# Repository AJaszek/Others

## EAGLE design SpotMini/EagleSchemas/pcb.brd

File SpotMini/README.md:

Projecting and creating own version of Boston Dynamics Spot

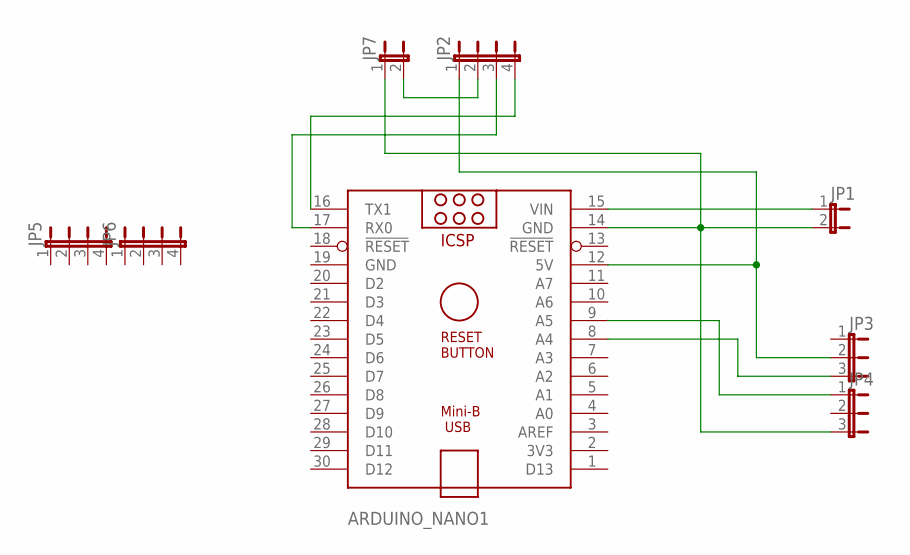
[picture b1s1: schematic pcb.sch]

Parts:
ARDUINO_NANO1: ARDUINO_NANO
JP1, JP7: JP1E; JP1
JP2, JP5, JP6: JP4E; JP4
JP3, JP4: JP2E; JP2

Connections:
GND: ARDUINO_NANO1.19 (GND)
unnamed: ARDUINO_NANO1.15 (VIN), JP1.1
unnamed: ARDUINO_NANO1.14 (GND), JP1.2, JP4.3, JP7.1
unnamed: ARDUINO_NANO1.12 (5V), JP2.1, JP3.2
unnamed: ARDUINO_NANO1.8 (A4), JP3.3
unnamed: ARDUINO_NANO1.9 (A5), JP4.1
unnamed: JP2.2, JP7.2
unnamed: ARDUINO_NANO1.17 (RX0), JP2.3
unnamed: ARDUINO_NANO1.16 (TX1), JP2.4

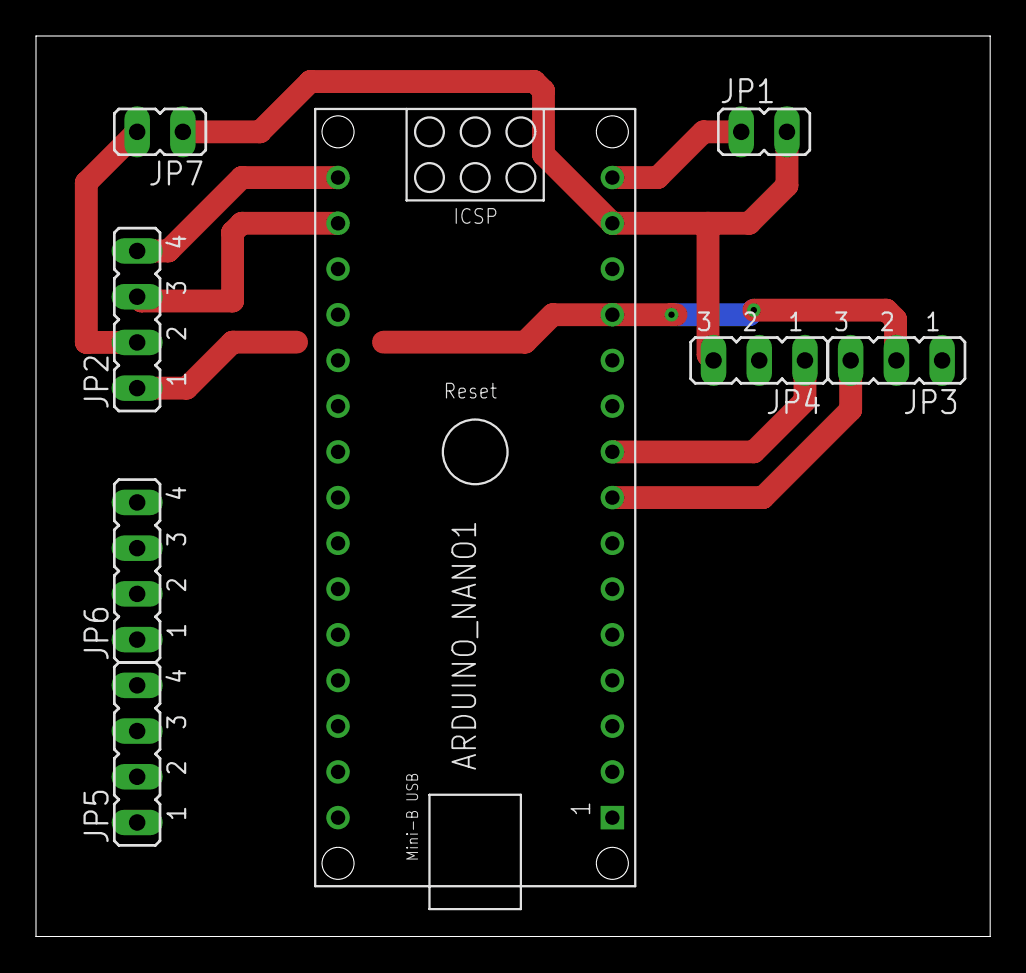
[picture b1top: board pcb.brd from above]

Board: 2 copper layers, 53.0 x 50.0 mm, 8 parts (0 on the bottom side), 8 nets.

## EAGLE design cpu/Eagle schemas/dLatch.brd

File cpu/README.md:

Projecting and creating my own 8-bit cpu

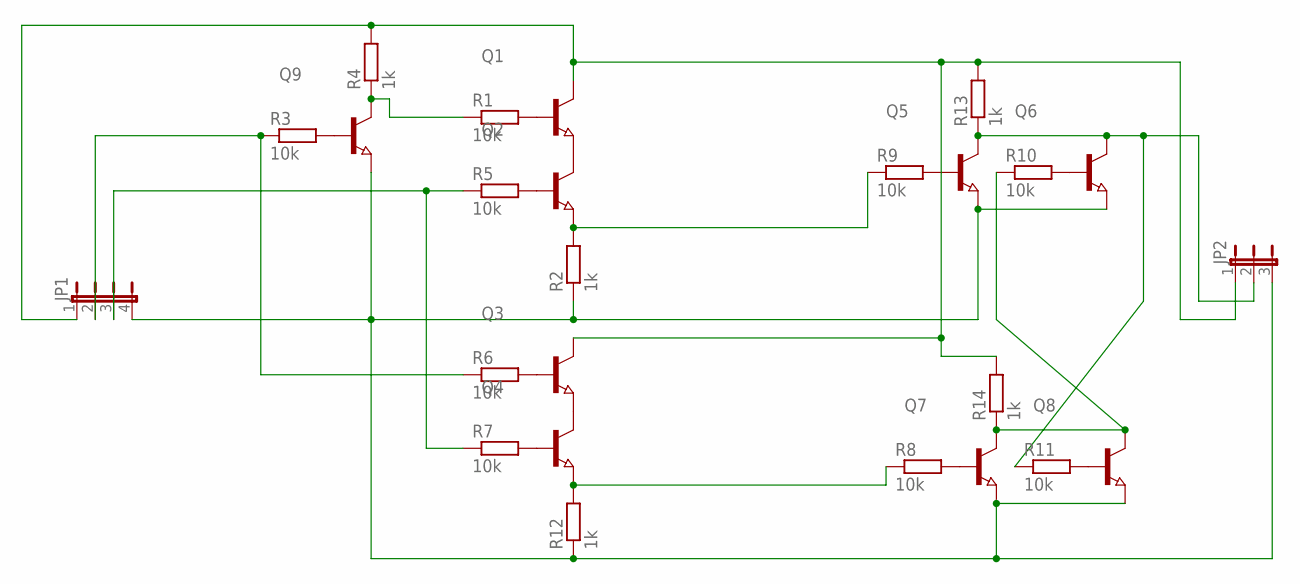
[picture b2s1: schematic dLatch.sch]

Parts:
JP1: JP4E; JP4
JP2: JP2W
Q1, Q2, Q3, Q4, Q5, Q6, Q7, Q8, Q9: NPN-TRANSISTOR_SOT23; SOT23
R1, R3, R5, R6, R7, R8, R9, R10, R11: 10k; R1206
R2, R4, R12, R13, R14: 1k; R1206

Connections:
unnamed: Q1.2 (E), Q2.3 (C)
unnamed: Q3.2 (E), Q4.3 (C)
unnamed: Q2.2 (E), R2.2, R9.1
unnamed: Q1.1 (B), R1.2
unnamed: Q9.1 (B), R3.2
unnamed: Q9.3 (C), R1.1, R4.1
unnamed: Q2.1 (B), R5.2
unnamed: Q3.1 (B), R6.2
unnamed: Q4.1 (B), R7.2
unnamed: Q7.1 (B), R8.2
unnamed: Q5.1 (B), R9.2
unnamed: Q6.1 (B), R10.2
unnamed: Q8.1 (B), R11.2
unnamed: Q4.2 (E), R8.1, R12.2
unnamed: JP2.2, Q5.3 (C), Q6.3 (C), R11.1, R13.1
unnamed: JP1.4, JP2.3, Q5.2 (E), Q6.2 (E), Q7.2 (E), Q8.2 (E), Q9.2 (E), R2.1, R12.1
unnamed: JP1.1, JP2.1, Q1.3 (C), Q3.3 (C), R4.2, R13.2, R14.2
unnamed: Q7.3 (C), Q8.3 (C), R10.1, R14.1
unnamed: JP1.2, R3.1, R6.1
unnamed: JP1.3, R5.1, R7.1

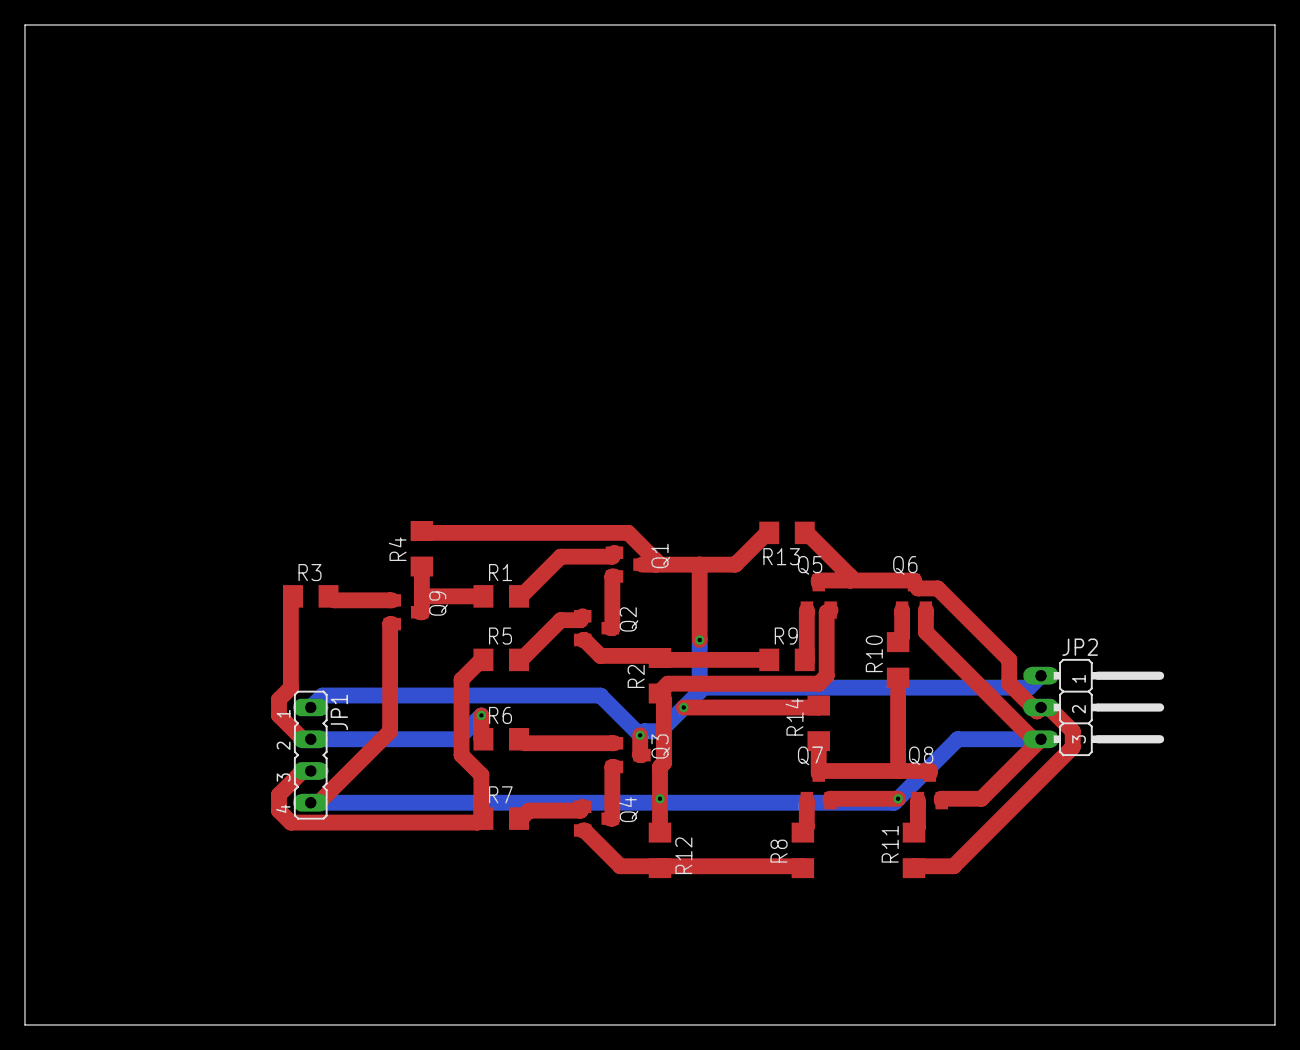
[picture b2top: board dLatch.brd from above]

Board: 2 copper layers, 100.0 x 80.0 mm, 25 parts (0 on the bottom side), 20 nets.

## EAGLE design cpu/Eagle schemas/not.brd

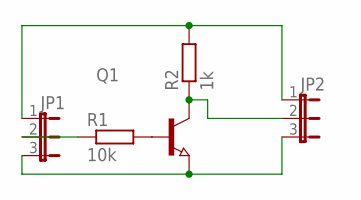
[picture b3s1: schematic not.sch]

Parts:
JP1, JP2: JP2W
Q1: NPN-TRANSISTOR_SOT23; SOT23
R1: 10k; R1206
R2: 1k; R1206

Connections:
unnamed: JP2.2, Q1.3 (C), R2.1
unnamed: Q1.1 (B), R1.2
unnamed: JP1.2, R1.1
unnamed: JP1.3, JP2.3, Q1.2 (E)
unnamed: JP1.1, JP2.1, R2.2

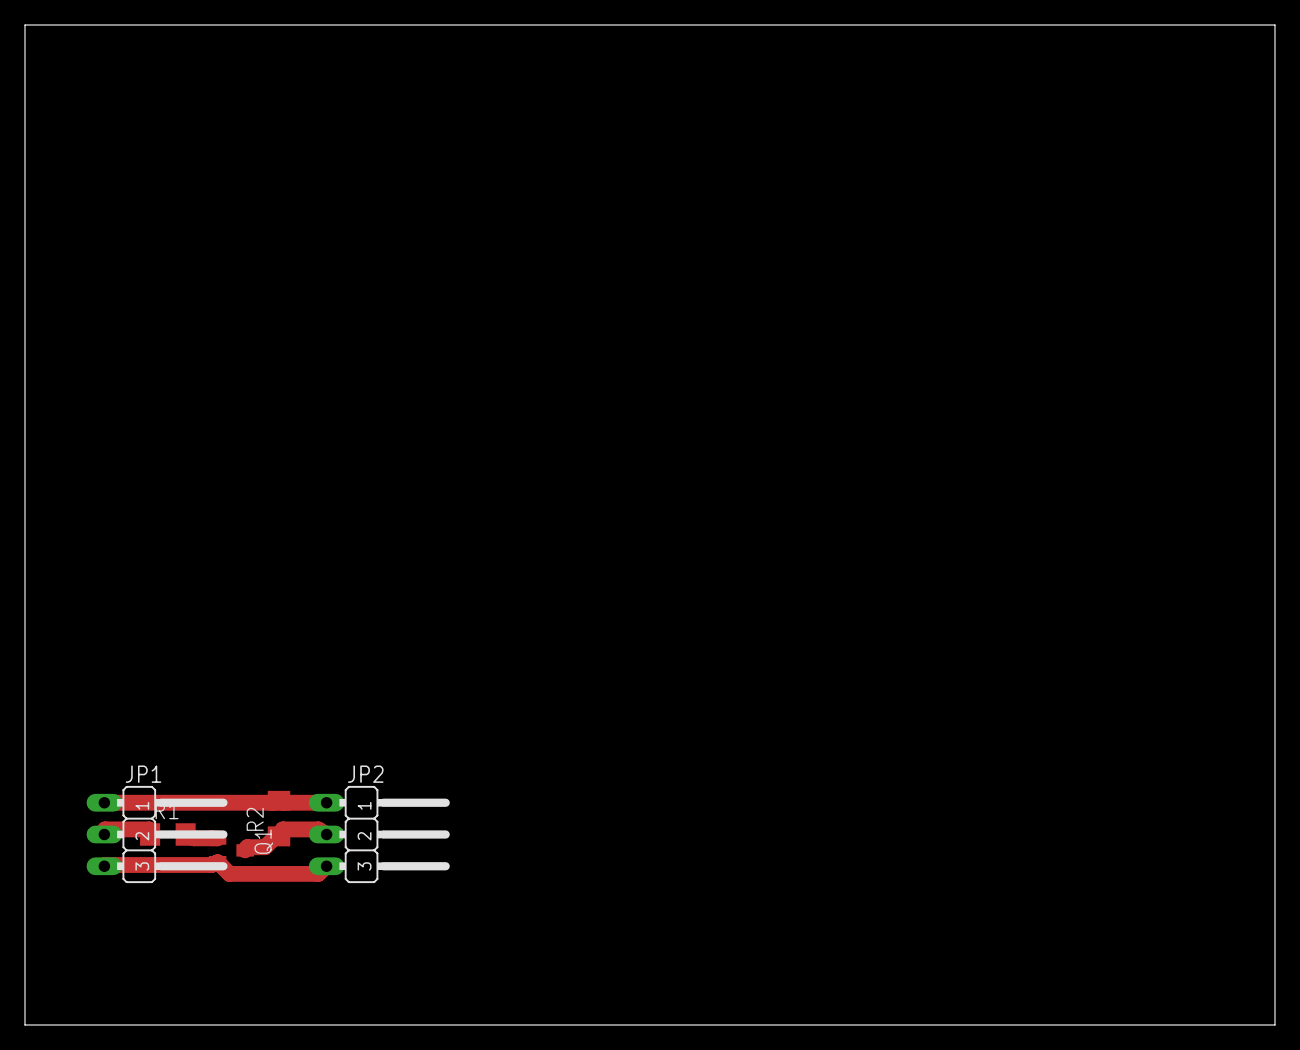
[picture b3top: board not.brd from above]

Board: 2 copper layers, 100.0 x 80.0 mm, 5 parts (0 on the bottom side), 5 nets.

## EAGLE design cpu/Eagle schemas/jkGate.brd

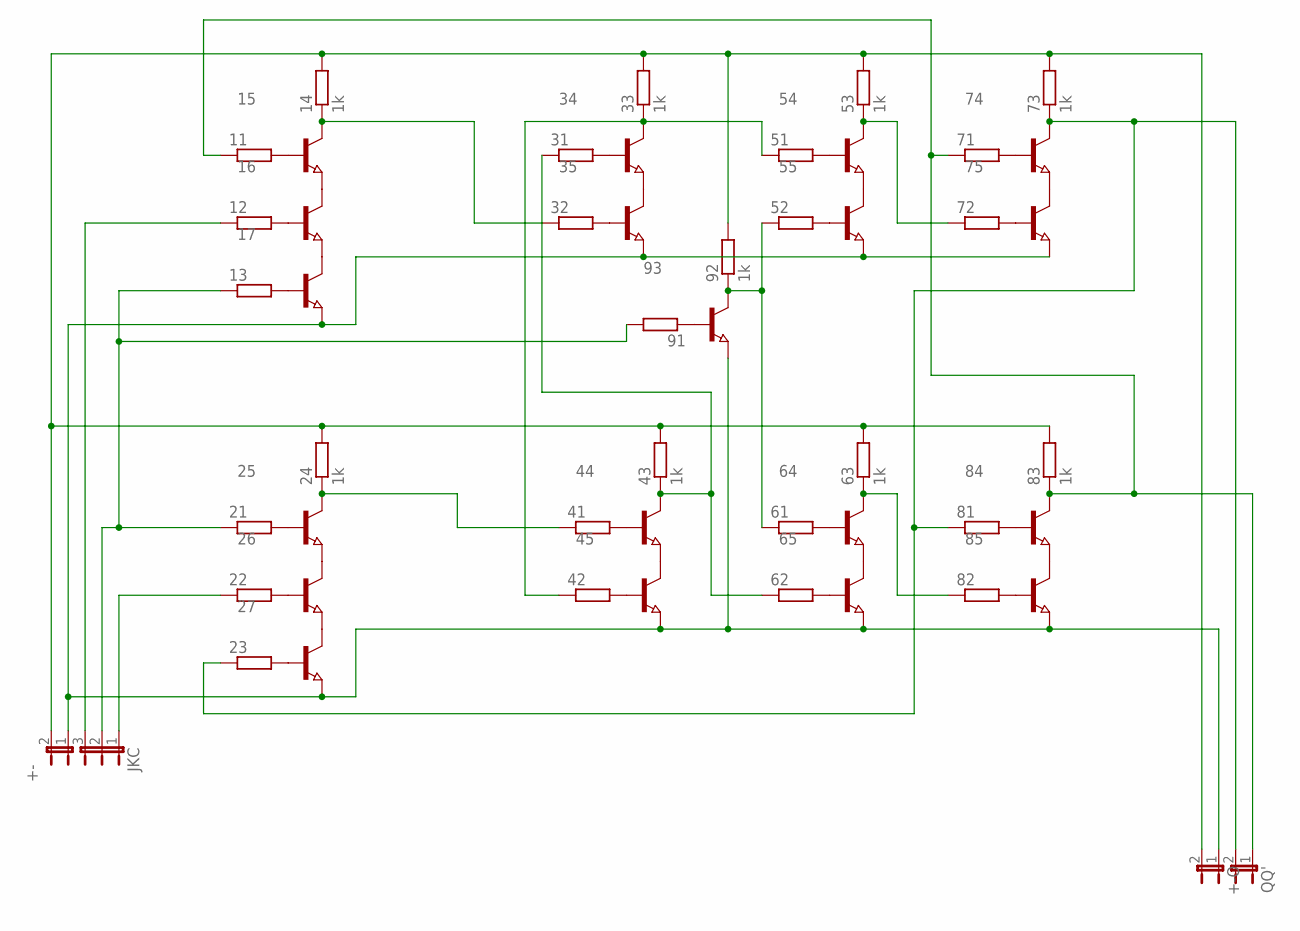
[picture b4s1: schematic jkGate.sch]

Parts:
11, 12, 13, 21, 22, 23, 31, 32, 41, 42, 51, 52, 61, 62, 71, 72, 81, 82, 91: R-EU_R1206; R1206
14, 24, 33, 43, 53, 63, 73, 83, 92: 1k; R1206
15, 16, 17, 25, 26, 27, 34, 35, 44, 45, 54, 55, 64, 65, 74, 75, 84, 85, 93: NPN-TRANSISTOR_SOT23; SOT23
+-: JP1E; JP1
+-O: JP1E; JP1
JKC: JP2E; JP2
QQ': JP1E; JP1

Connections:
5V: 14.2, 24.2, 33.2, 43.2, 53.2, 63.2, 73.2, 83.2, 92.2, +-.2, +-O.2
C: 13.1, 21.1, 91.2, JKC.2
GND: 17.2 (E), 27.2 (E), 35.2 (E), 45.2 (E), 55.2 (E), 65.2 (E), 75.2 (E), 85.2 (E), 93.2 (E), +-.1, +-O.1
J: 12.1, JKC.3
K: 22.1, JKC.1
unnamed: 15.2 (E), 16.3 (C)
unnamed: 16.2 (E), 17.3 (C)
unnamed: 25.2 (E), 26.3 (C)
unnamed: 26.2 (E), 27.3 (C)
unnamed: 34.2 (E), 35.3 (C)
unnamed: 44.2 (E), 45.3 (C)
unnamed: 54.2 (E), 55.3 (C)
unnamed: 64.2 (E), 65.3 (C)
unnamed: 74.2 (E), 75.3 (C)
unnamed: 84.2 (E), 85.3 (C)
unnamed: 21.2, 25.1 (B)
unnamed: 22.2, 26.1 (B)
unnamed: 23.2, 27.1 (B)
unnamed: 11.2, 15.1 (B)
unnamed: 12.2, 16.1 (B)
unnamed: 13.2, 17.1 (B)
unnamed: 31.2, 34.1 (B)
unnamed: 32.2, 35.1 (B)
unnamed: 51.2, 54.1 (B)
unnamed: 52.2, 55.1 (B)
unnamed: 71.2, 74.1 (B)
unnamed: 72.2, 75.1 (B)
unnamed: 81.2, 84.1 (B)
unnamed: 82.2, 85.1 (B)
unnamed: 61.2, 64.1 (B)
unnamed: 62.2, 65.1 (B)
unnamed: 41.2, 44.1 (B)
unnamed: 42.2, 45.1 (B)
unnamed: 24.1, 25.3 (C), 41.1
unnamed: 31.1, 43.1, 44.3 (C), 62.1
unnamed: 63.1, 64.3 (C), 82.1
unnamed: 11.1, 71.1, 83.1, 84.3 (C), QQ'.1
unnamed: 14.1, 15.3 (C), 32.1
unnamed: 33.1, 34.3 (C), 42.1, 51.1
unnamed: 53.1, 54.3 (C), 72.1
unnamed: 23.1, 73.1, 74.3 (C), 81.1, QQ'.2
unnamed: 52.1, 61.1, 92.1, 93.3 (C)
unnamed: 91.1, 93.1 (B)

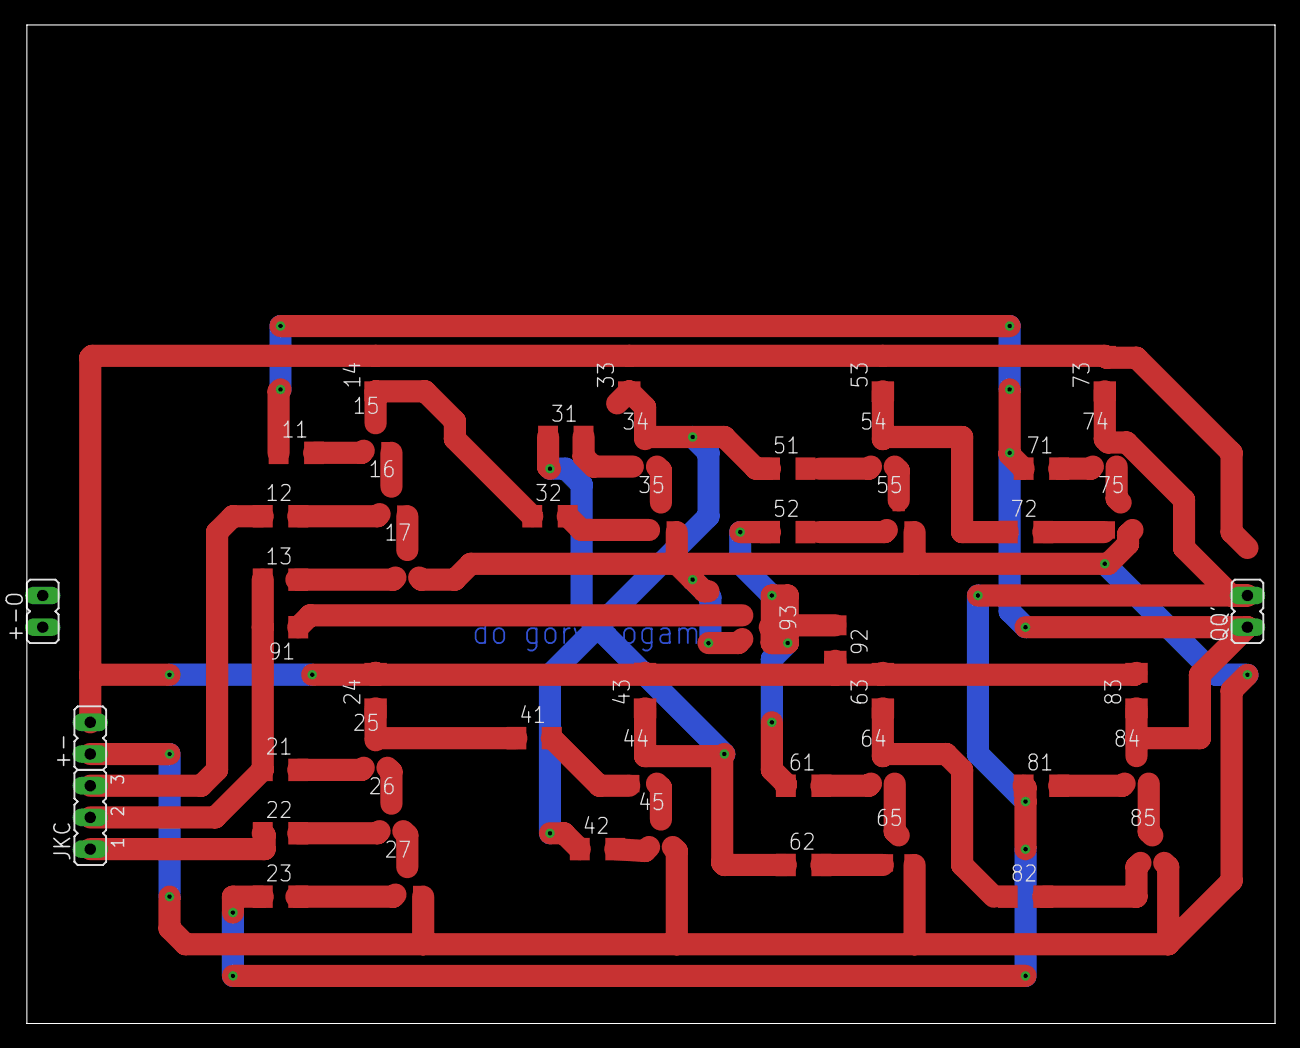
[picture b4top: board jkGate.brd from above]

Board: 2 copper layers, 100.0 x 80.0 mm, 51 parts (0 on the bottom side), 43 nets.

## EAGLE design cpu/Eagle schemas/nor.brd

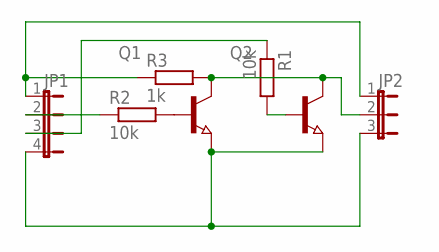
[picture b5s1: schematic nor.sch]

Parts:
JP1: JP4E; JP4
JP2: JP2W
Q1, Q2: NPN-TRANSISTOR_SOT23; SOT23
R1, R2: 10k; R1206
R3: 1k; R1206

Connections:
unnamed: Q2.1 (B), R1.2
unnamed: Q1.1 (B), R2.2
unnamed: JP1.4, JP2.3, Q1.2 (E), Q2.2 (E)
unnamed: JP2.2, Q1.3 (C), Q2.3 (C), R3.2
unnamed: JP1.2, R2.1
unnamed: JP1.3, R1.1
unnamed: JP1.1, JP2.1, R3.1

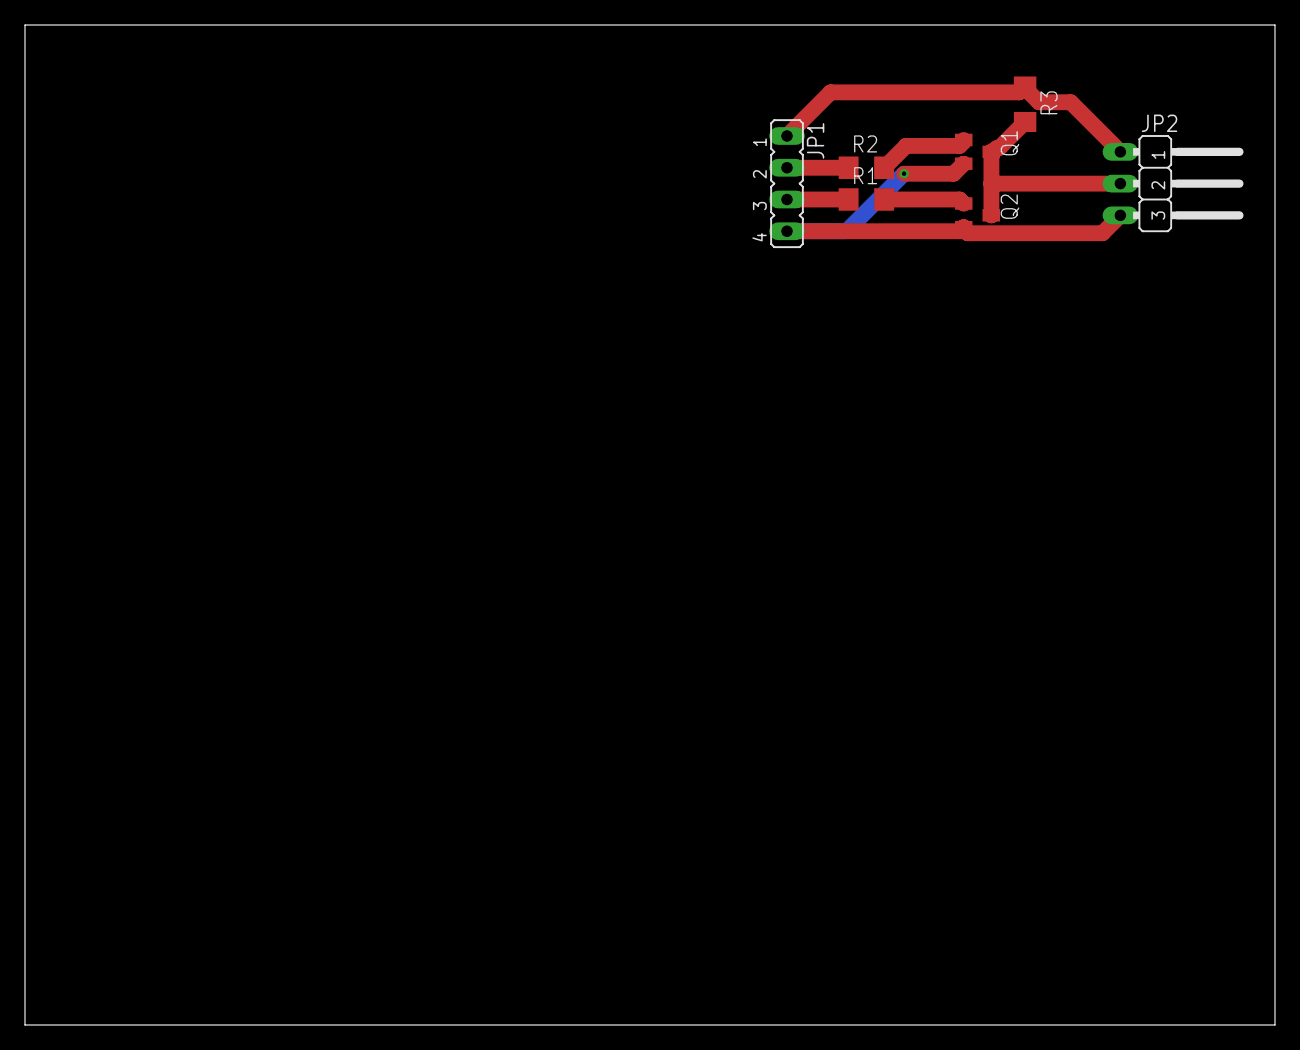
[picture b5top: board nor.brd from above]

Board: 2 copper layers, 100.0 x 80.0 mm, 7 parts (0 on the bottom side), 7 nets.

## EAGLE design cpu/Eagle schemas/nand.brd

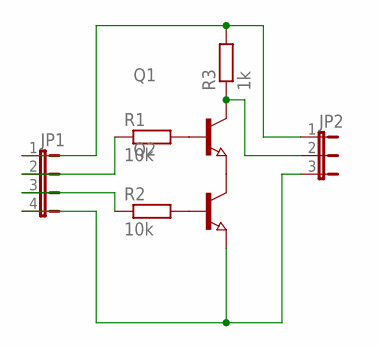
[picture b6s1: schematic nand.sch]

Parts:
JP1: JP4E; JP4
JP2: JP2W
Q1, Q2: NPN-TRANSISTOR_SOT23; SOT23
R1, R2: 10k; R1206
R3: 1k; R1206

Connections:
unnamed: Q1.2 (E), Q2.3 (C)
unnamed: Q1.1 (B), R1.2
unnamed: Q2.1 (B), R2.2
unnamed: JP1.2, R1.1
unnamed: JP1.3, R2.1
unnamed: JP1.4, JP2.3, Q2.2 (E)
unnamed: JP1.1, JP2.1, R3.2
unnamed: JP2.2, Q1.3 (C), R3.1

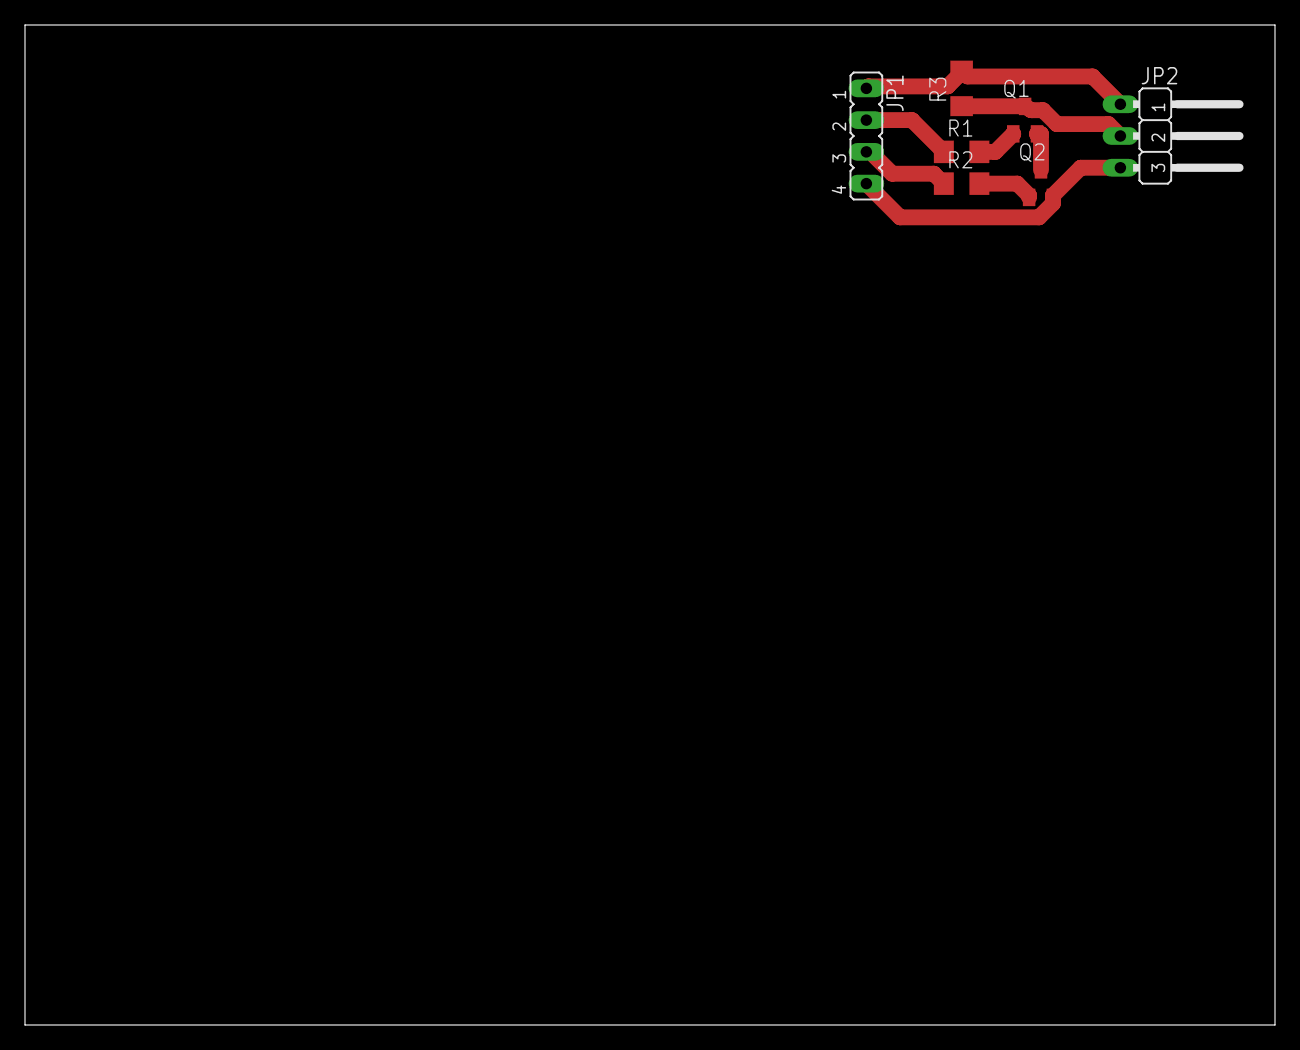
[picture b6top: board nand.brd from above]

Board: 2 copper layers, 100.0 x 80.0 mm, 7 parts (0 on the bottom side), 8 nets.

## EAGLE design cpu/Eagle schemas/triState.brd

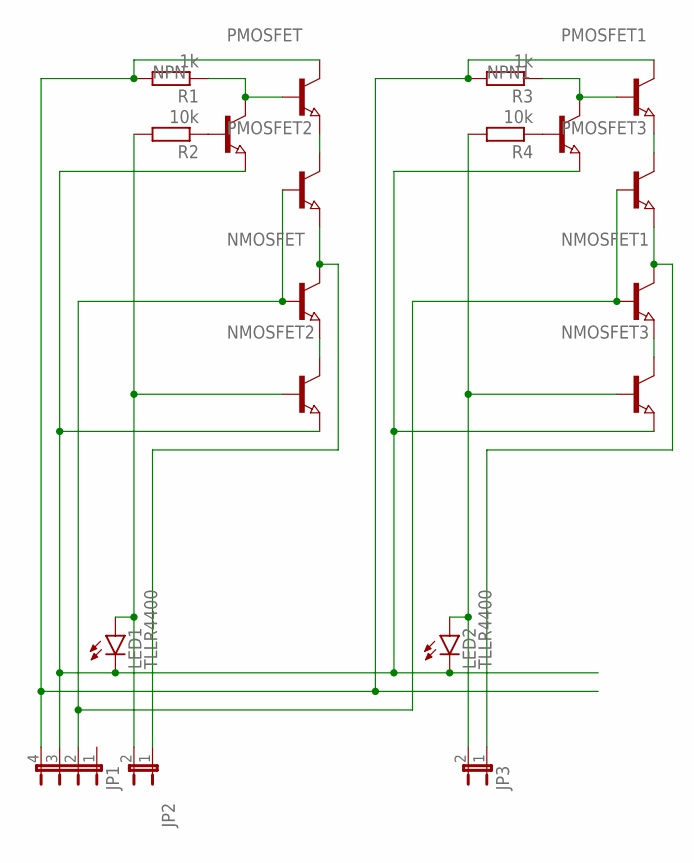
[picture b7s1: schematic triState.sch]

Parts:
JP1: JP4E; JP4
JP2, JP3: JP1E; JP1
LED1, LED2: TLLR4400; LED3MM
NMOSFET, NMOSFET1, NMOSFET2, NMOSFET3: NPN-TRANSISTOR_SOT23; SOT23
NPN, NPN1: NPN-TRANSISTOR_SOT23; SOT23
PMOSFET, PMOSFET1, PMOSFET2, PMOSFET3: NPN-TRANSISTOR_SOT23; SOT23
R1, R3: 1k; R1206
R2, R4: 10k; R1206

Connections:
DI0: JP2.2, LED1.A, NMOSFET2.1 (B), R2.2
DI1: JP3.2, LED2.A, NMOSFET3.1 (B), R4.2
DO0: JP2.1, NMOSFET.3 (C), PMOSFET2.2 (E)
DO1: JP3.1, NMOSFET1.3 (C), PMOSFET3.2 (E)
GND: JP1.3, LED1.K (C), LED2.K (C), NMOSFET2.2 (E), NMOSFET3.2 (E), NPN.2 (E), NPN1.2 (E)
unnamed: NPN.3 (C), PMOSFET.1 (B), R1.1
unnamed: NPN.1 (B), R2.1
unnamed: PMOSFET.2 (E), PMOSFET2.3 (C)
unnamed: NMOSFET.2 (E), NMOSFET2.3 (C)
unnamed: NPN1.1 (B), R4.1
unnamed: NPN1.3 (C), PMOSFET1.1 (B), R3.1
unnamed: PMOSFET1.2 (E), PMOSFET3.3 (C)
unnamed: NMOSFET1.2 (E), NMOSFET3.3 (C)
OE: JP1.2, NMOSFET.1 (B), NMOSFET1.1 (B), PMOSFET2.1 (B), PMOSFET3.1 (B)
VCC: JP1.4, PMOSFET.3 (C), PMOSFET1.3 (C), R1.2, R3.2

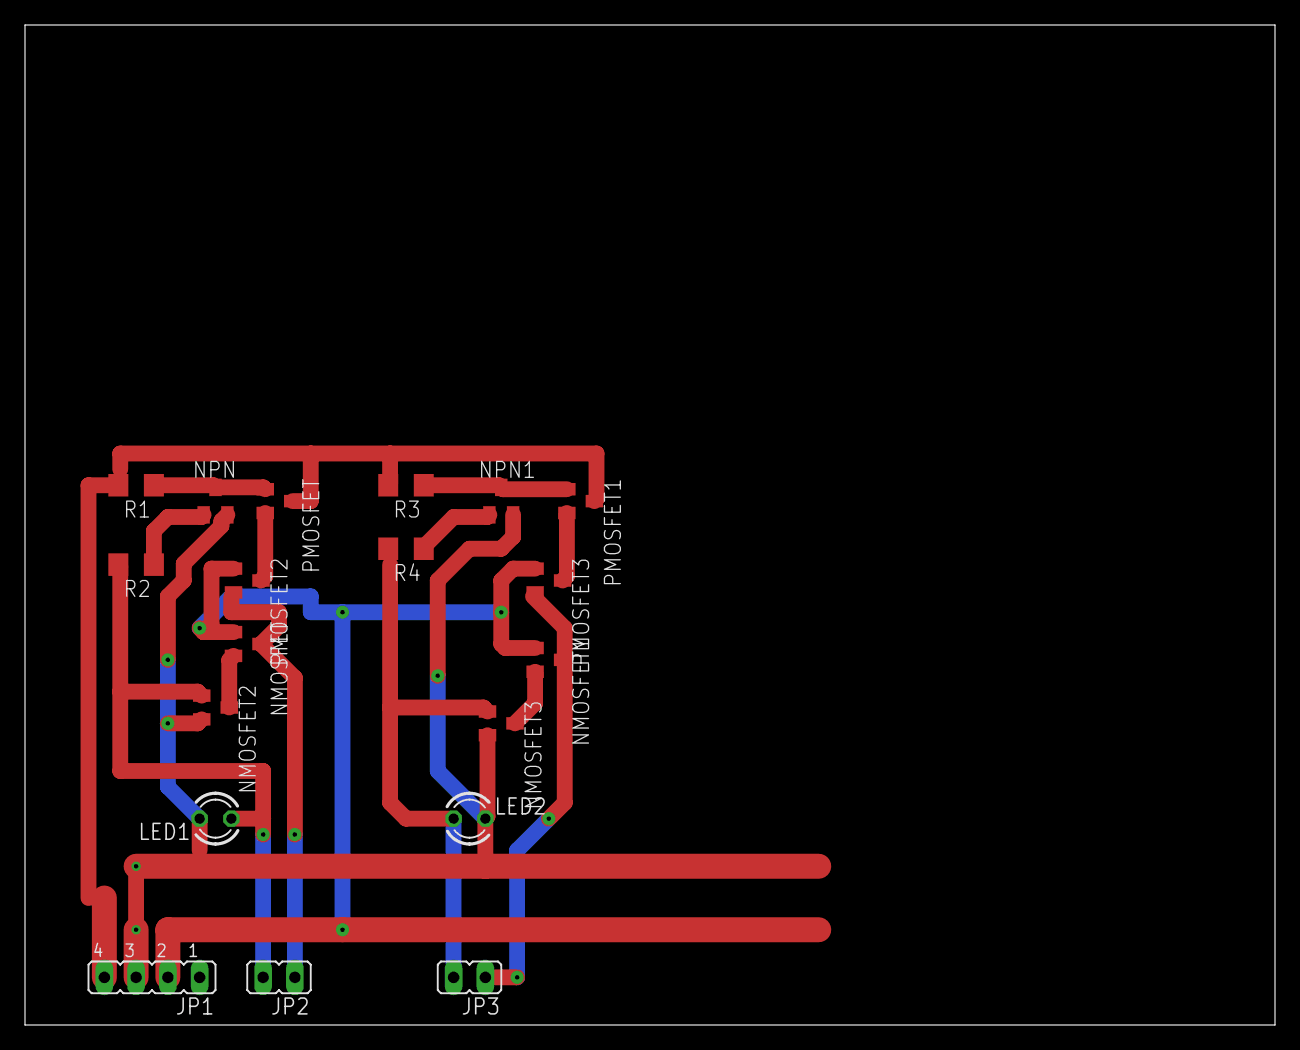
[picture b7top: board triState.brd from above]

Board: 2 copper layers, 100.0 x 80.0 mm, 19 parts (0 on the bottom side), 15 nets.

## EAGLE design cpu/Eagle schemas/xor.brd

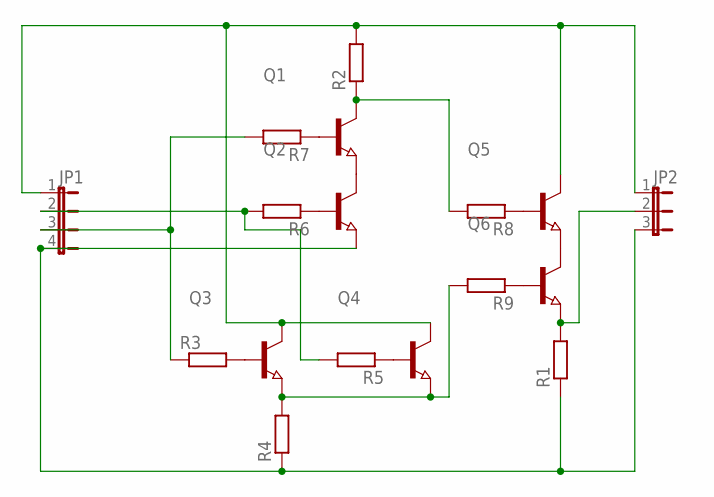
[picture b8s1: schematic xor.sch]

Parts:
JP1: JP4E; JP4
JP2: JP2W
Q1, Q2, Q3, Q4, Q5, Q6: NPN-TRANSISTOR_SOT23; SOT23
R1, R2, R3, R4, R5, R6, R7, R8, R9: R-EU_R1206; R1206

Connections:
unnamed: Q1.2 (E), Q2.3 (C)
unnamed: Q5.2 (E), Q6.3 (C)
unnamed: JP2.2, Q6.2 (E), R1.2
unnamed: Q1.3 (C), R2.1, R8.2
unnamed: Q3.1 (B), R3.2
unnamed: Q4.1 (B), R5.1
unnamed: Q2.1 (B), R6.1
unnamed: Q1.1 (B), R7.1
unnamed: Q5.1 (B), R8.1
unnamed: Q6.1 (B), R9.1
unnamed: JP1.1, JP2.1, Q3.3 (C), Q4.3 (C), Q5.3 (C), R2.2
unnamed: Q3.2 (E), Q4.2 (E), R4.2, R9.2
unnamed: JP1.4, JP2.3, Q2.2 (E), R1.1, R4.1
unnamed: JP1.2, R5.2, R6.2
unnamed: JP1.3, R3.1, R7.2

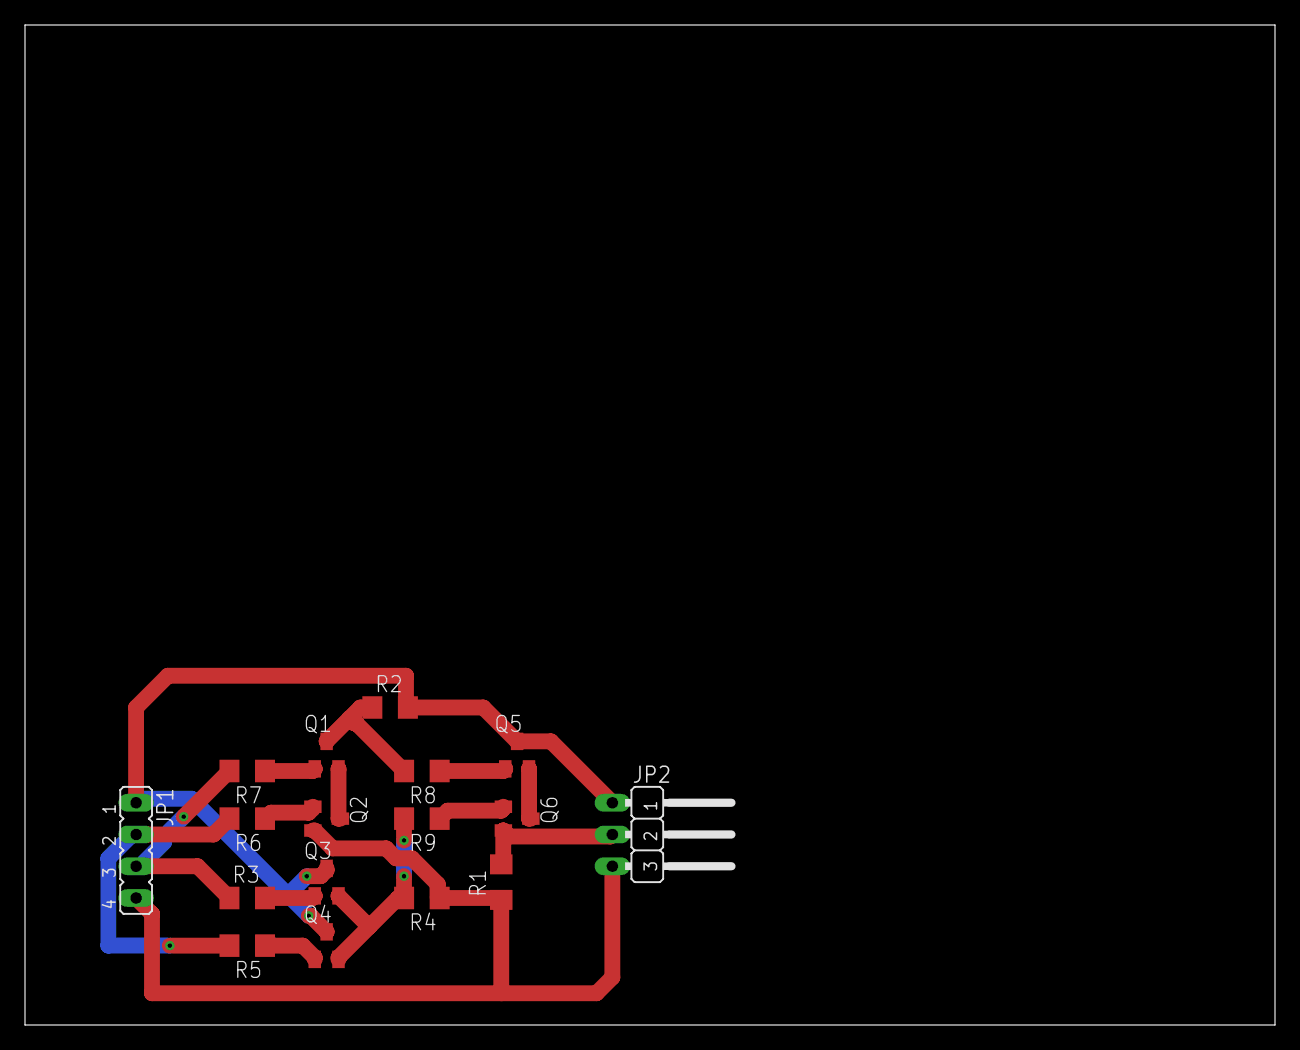
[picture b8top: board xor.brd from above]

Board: 2 copper layers, 100.0 x 80.0 mm, 17 parts (0 on the bottom side), 15 nets.

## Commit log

2021-06-02 Updated font and questionnaire refil button
2023-12-17 Created auto incrementing numbers script
    Script which allow to paste own text concatenated with auto increment numbers. Next number increase each time of paste text.
